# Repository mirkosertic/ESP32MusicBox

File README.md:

# ESP32 MusicBox

This project provides an ESP32 based music box with the following features:

* Simple 3-button control
* MP3 playback
* Integration with I2C RFID tag scanner
* Support for WiFi Grids with auto-reconnect to nearest access point
* MQTT status reporting / remote control
* Home Assistant integration with device autodiscovery
* Web-based user interface
* Integrated into your local network with SSDP / mDNS protocol
* WebDAV support for file / content management
* Optional Bluetooth A2DP output / Bluetooth Headphone output
* Special mode to start in Bluetooth Speaker mode, so it works as a Boombox.
* 3-band equalizer

## Supported hardware

* ESP32 (tested with Lolin D32 Pro with a lot of PSRAM recommended (8 MB), 4MB flash RAM is required)
* PN532 RFID Reader (i2c-Mode)
* SDCard Reader (SPI-Mode), is already mounted on a Lolin D32 Pro board
* NeoPixel / WS2812 based LEDs for status visualization

## Final product

The KiCad 9.0 project is located in the kicad folder.

Here is the wiring schematic drawing:

## Manual

Status visualization with LEDs:

- Boot-Sequence - LEDs enabled step by step to visualize boot progress
- Leds cycling in brightness - orange in case WiFi is not connected but enabled, green in case if playback paused or no playback yet
- Leds green from 0% to 100% filling the circle - Playback progress while playing something
- Leds blinking red - Unknown RFID card detected
- Leds blinking green - RFID card programmed / Known card detected
- Leds green to red - While changing volume
- Keep button 1 pressed during startup. Leds will turn blue to indicate Bluetooth Speaker mode.
- Yellow flashing LEDs indicate a Bluetooth pairing request while in Speaker mode. Press button 1 again to confirm the pairing. LEDs will flash in blue to confirm pairing
- Keep button 1 and button 2 pressed during playback to start from beginning

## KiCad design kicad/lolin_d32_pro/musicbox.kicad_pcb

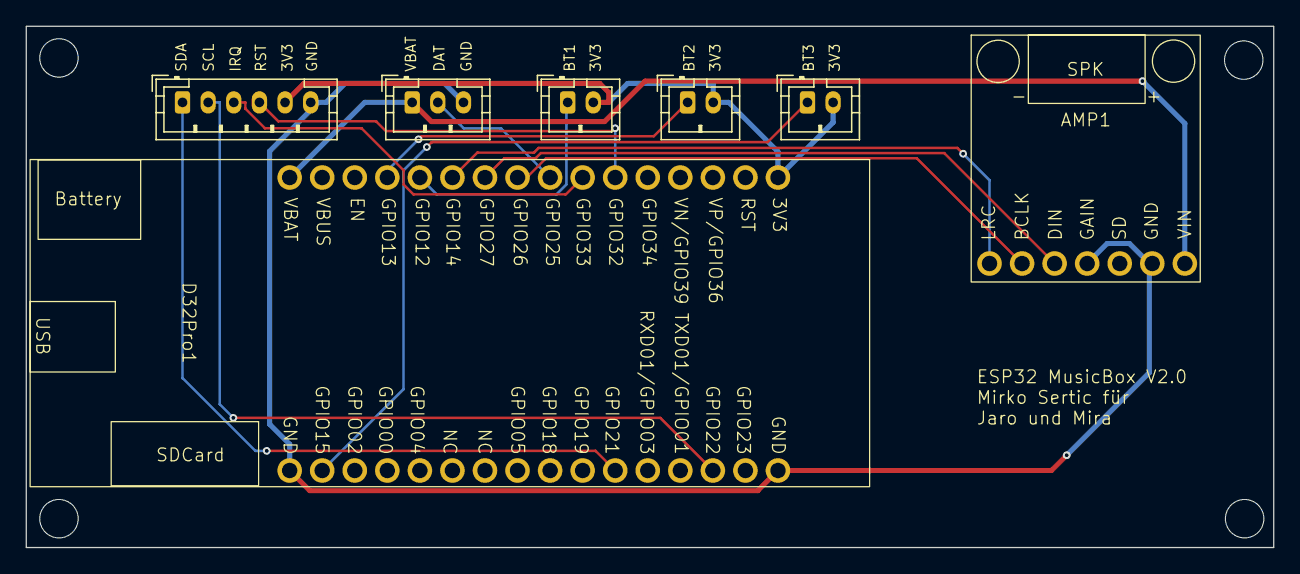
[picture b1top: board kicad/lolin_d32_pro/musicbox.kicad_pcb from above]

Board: 2 copper layers, 97.3 x 40.7 mm, 7 parts (0 on the bottom side), 14 nets.

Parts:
AMP1: MAX98357A
BT1Con1, BT2Con1, BT3Con1: JST_PH_B2B-PH-K_1x02_P2.00mm_Vertical
D32Pro1: ESPD32Pro
NeoPixelCon1: JST_PH_B3B-PH-K_1x03_P2.00mm_Vertical
RFIDCon1: Conn_01x06_Socket; JST_PH_B6B-PH-K_1x06_P2.00mm_Vertical

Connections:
3V3: BT1Con1.2, BT2Con1.2, BT3Con1.2, D32Pro1.1 (3V3), RFIDCon1.5
/ADR_LED: D32Pro1.8 (GPIO25), NeoPixelCon1.2
/BT1: BT1Con1.1, D32Pro1.12 (GPIO12)
/BT2: BT2Con1.1, D32Pro1.13 (GPIO13)
/BT3: BT3Con1.1, D32Pro1.31 (GPIO15)
/I2C_SCL: D32Pro1.19 (GPIO22), RFIDCon1.2
/I2C_SDA: D32Pro1.22 (GPIO21), RFIDCon1.1
/I2S_BCK: AMP1.2 (BCLK), D32Pro1.9 (GPIO26)
/I2S_DIN: AMP1.3 (DIN), D32Pro1.10 (GPIO27)
/I2S_WS: AMP1.1 (LRC), D32Pro1.11 (GPIO14)
/RFID_IRQ: D32Pro1.7 (GPIO33), RFIDCon1.3
/RFID_RST: D32Pro1.6 (GPIO32), RFIDCon1.4
GND: AMP1.4 (GAIN), AMP1.6 (GND), D32Pro1.17 (GND), D32Pro1.32 (GND), NeoPixelCon1.3, RFIDCon1.6
VBAT: AMP1.7 (VIN), D32Pro1.16 (VBAT), NeoPixelCon1.1

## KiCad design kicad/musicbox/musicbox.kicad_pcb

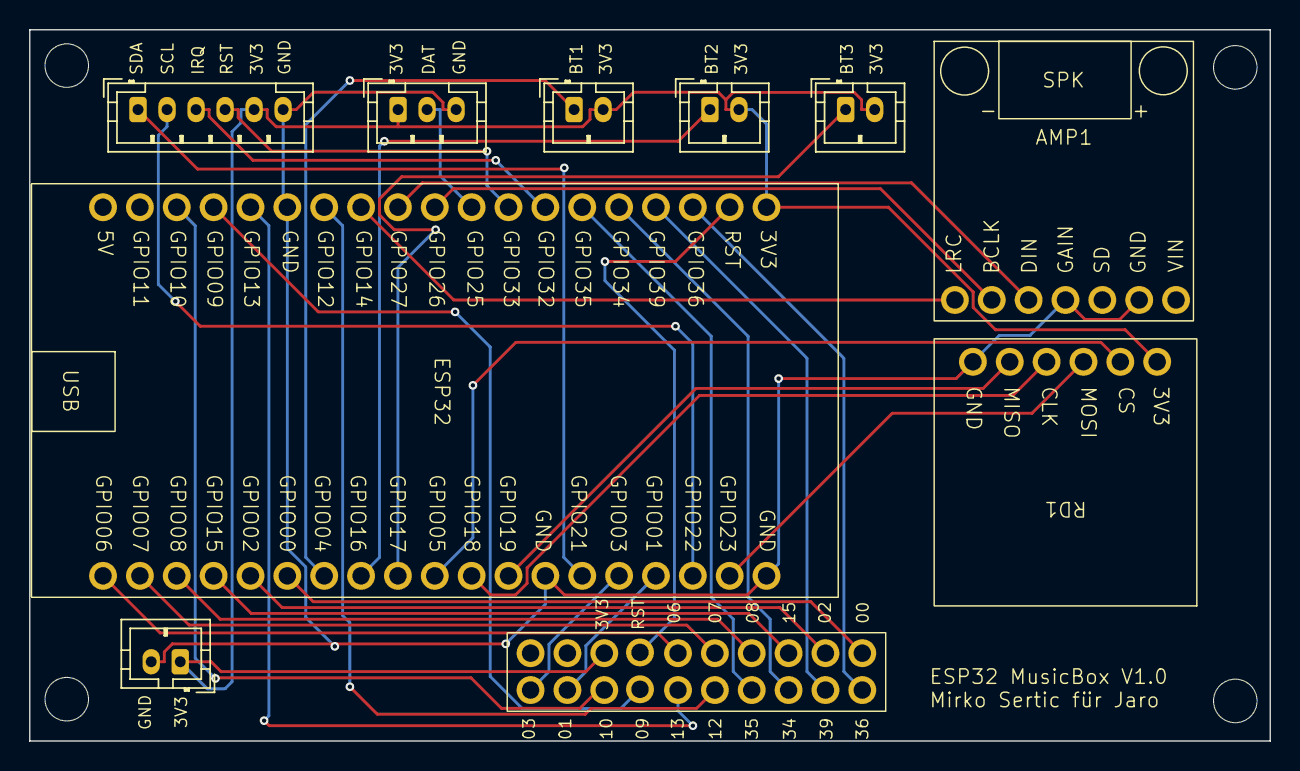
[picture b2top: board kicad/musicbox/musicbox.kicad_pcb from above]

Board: 2 copper layers, 85.5 x 49.0 mm, 10 parts (0 on the bottom side), 34 nets.

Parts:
AMP1: MAX98357A
BT1Con1, BT2Con1, BT3Con1: JST_PH_B2B-PH-K_1x02_P2.00mm_Vertical
ESP32: ESP32DevKit
IO1: IO; Pads_2x10
NeoPixelCon1: JST_PH_B3B-PH-K_1x03_P2.00mm_Vertical
PWRCon1: JST_PH_B2B-PH-K_1x02_P2.00mm_Vertical
RD1: SDCardReader
RFIDCon1: Conn_01x06_Socket; JST_PH_B6B-PH-K_1x06_P2.00mm_Vertical

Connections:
3V3: BT1Con1.2, BT2Con1.2, BT3Con1.2, ESP32.1 (3V3), IO1.18, NeoPixelCon1.1, PWRCon1.1, RD1.1 (VCC), RFIDCon1.5
/ADR_LED: ESP32.9 (GPIO25), NeoPixelCon1.2
/BT1: BT1Con1.1, ESP32.32 (GPIO04)
/BT2: BT2Con1.1, ESP32.31 (GPIO16)
/BT3: BT3Con1.1, ESP32.30 (GPIO17)
/GPIO00: ESP32.33 (GPIO00), IO1.11
/GPIO01: ESP32.23 (GPIO01), IO1.9
/GPIO02: ESP32.34 (GPIO02), IO1.12
/GPIO03: ESP32.24 (GPIO03), IO1.10
/GPIO06: ESP32.38 (GPIO06), IO1.16
/GPIO07: ESP32.37 (GPIO07), IO1.15
/GPIO08: ESP32.36 (GPIO08), IO1.14
/GPIO09: ESP32.16 (GPIO09), IO1.7
/GPIO10: ESP32.17 (GPIO10), IO1.8
/GPIO12: ESP32.13 (GPIO12), IO1.5
/GPIO13: ESP32.15 (GPIO13), IO1.6
/GPIO15: ESP32.35 (GPIO15), IO1.13
/GPIO34: ESP32.5 (GPIO34), IO1.3
/GPIO35: ESP32.6 (GPIO35), IO1.4
/GPIO36: ESP32.3 (GPIO36), IO1.1
/GPIO39: ESP32.4 (GPIO39), IO1.2
/I2C_SCL: ESP32.22 (GPIO22), RFIDCon1.2
/I2C_SDA: ESP32.25 (GPIO21), RFIDCon1.1
/I2S_BCK: AMP1.2 (BCLK), ESP32.10 (GPIO26)
/I2S_DIN: AMP1.3 (DIN), ESP32.11 (GPIO27)
/I2S_WS: AMP1.1 (LRC), ESP32.12 (GPIO14)
/RFID_IRQ: ESP32.7 (GPIO32), RFIDCon1.3
/RFID_RST: ESP32.8 (GPIO33), RFIDCon1.4
/RST: ESP32.2 (RESET), IO1.17
/SPI_MISO: ESP32.27 (GPIO19), RD1.5 (MISO)
/SPI_MOSI: ESP32.21 (GPIO23), RD1.3 (MOSI)
/SPI_SCK: ESP32.28 (GPIO18), RD1.4 (SCK)
/SPI_SS: ESP32.29 (GPIO05), RD1.2 (CS)
GND: AMP1.4 (GAIN), AMP1.6 (GND), ESP32.14 (GND), ESP32.20 (GND), ESP32.26 (GND), NeoPixelCon1.3, PWRCon1.2, RD1.6 (GND), RFIDCon1.6

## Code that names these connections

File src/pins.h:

#ifndef PINS_H
#define PINS_H

// Make sure the the buttons are assigned to IO pins with pullup/puppdown resistors configurable by software!
// RTC GPIO for Deepsleep Wakeup
#define GPIO_STARTSTOP GPIO_NUM_12
#define GPIO_PREVIOUS  GPIO_NUM_13
#define GPIO_NEXT	   GPIO_NUM_15

#define GPIO_WIRE_SDA GPIO_NUM_21
#define GPIO_WIRE_SCL GPIO_NUM_22

// RTC GPIO for Deepsleep Wakeup
#define GPIO_PN532_IRQ GPIO_NUM_33
#define GPIO_PN532_RST GPIO_NUM_32

#define GPIO_NEOPIXEL_DATA GPIO_NUM_25

#define GPIO_I2S_BCK  GPIO_NUM_26
#define GPIO_I2S_WS	  GPIO_NUM_14
#define GPIO_I2S_DATA GPIO_NUM_27

#define GPIO_SPI_SS	  GPIO_NUM_4
#define GPIO_SPI_SCK  GPIO_NUM_18
#define GPIO_SPI_MOSI GPIO_NUM_23
#define GPIO_SPI_MISO GPIO_NUM_19

// analogRead(GPIO_VOLTAGE_MEASURE) / 4096.0 * 7.445
#define GPIO_VOLTAGE_MEASURE GPIO_NUM_35

#endif

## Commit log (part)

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2024-09-18 Migrated to SD_MMC / Added better logging
2024-09-19 VoiceAssistant integration prototype
2024-09-20 Working on threading issues...
2024-09-20 Threading fix
2024-09-20 Working on threading issues
2024-09-21 Working von Voice Assistant threading
2024-09-21 Working on audio assistant
2024-09-21 Reactivate WLAN scanner
2024-09-22 Bug Fixing
2024-09-22 Added microphone volume setting
2024-09-25 Bug fixing voice assistant integration
2024-09-28 Refactored MQTT logic into separate class
2024-09-28 Refactored button control logic into separate class
2024-09-30 Debugging and bug fixing
2024-10-27 Bug fixing / added KiCad project
2024-10-27 Updated the documentation
2024-10-31 Working on visual feedback using NeoPixels
2024-10-31 Aktualisieren von platformio.ini
2024-11-01 Library version fix
2025-05-26 Working on newer prototype
2025-05-26 Working on newer version
2025-05-28 Working on ewer version
2025-06-05 Bug fixing / WebDAV
2025-06-18 BUg fixing / BT speaker mode support
2025-06-19 Working on Bluetooth integration
2025-06-19 Fixed speaker volume level
2025-06-22 Working on Bluetooth Speaker mode
2025-06-22 Compile errors
2025-06-22 Fixing file naming
2025-06-23 Updated Gerbers for Lolin D32 Pro
2025-06-24 Working on documentation
2025-06-26 Improving code structure
2025-06-30 Bug fixing in WebDAV implementation
2025-07-06 Bug fixed deepsleep implementation
2025-07-08 Bug fixing deepsleep implementation
2025-07-09 Bug fixing automatic network disconnect
2025-07-09 Setting the correct hostname
2025-07-10 Preparing Webradio support
2025-07-13 Bug fixing volume control
2025-07-21 Added equalizer
2025-07-22 Testing LED colors
2025-07-24 Storing last play index per directory on SD
2025-07-25 Using another button for bluetooth functionalities
2025-07-25 Bug fix : wrong playback direction after navigation
2025-07-27 Use last playyback after reboot
2025-07-28 Use last playback after reboot
2025-08-02 Bug fix in prev button navigation
2025-08-02 Fixed color playback progress indicator
2025-11-01 Added playback reset functionality and reversed led order
2025-11-02 Optimized WiFi connectivity
2025-12-25 Bug fix
2025-12-25 Lib updates
2026-01-29 Updated to ESP-IDF 5 / Core 3
2026-03-13 Bug fixing / library updates
2026-03-19 Fixing Volume Display
2026-04-17 Update dependabot configuration for package ecosystem
2026-04-17 Added pullrequest workflow
2026-04-26 Configure Dependabot for GitHub Actions
    Added configuration for GitHub Actions dependency updates.
